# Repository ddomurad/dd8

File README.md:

# dd8
6502 based 8bit computer. 
TBD.

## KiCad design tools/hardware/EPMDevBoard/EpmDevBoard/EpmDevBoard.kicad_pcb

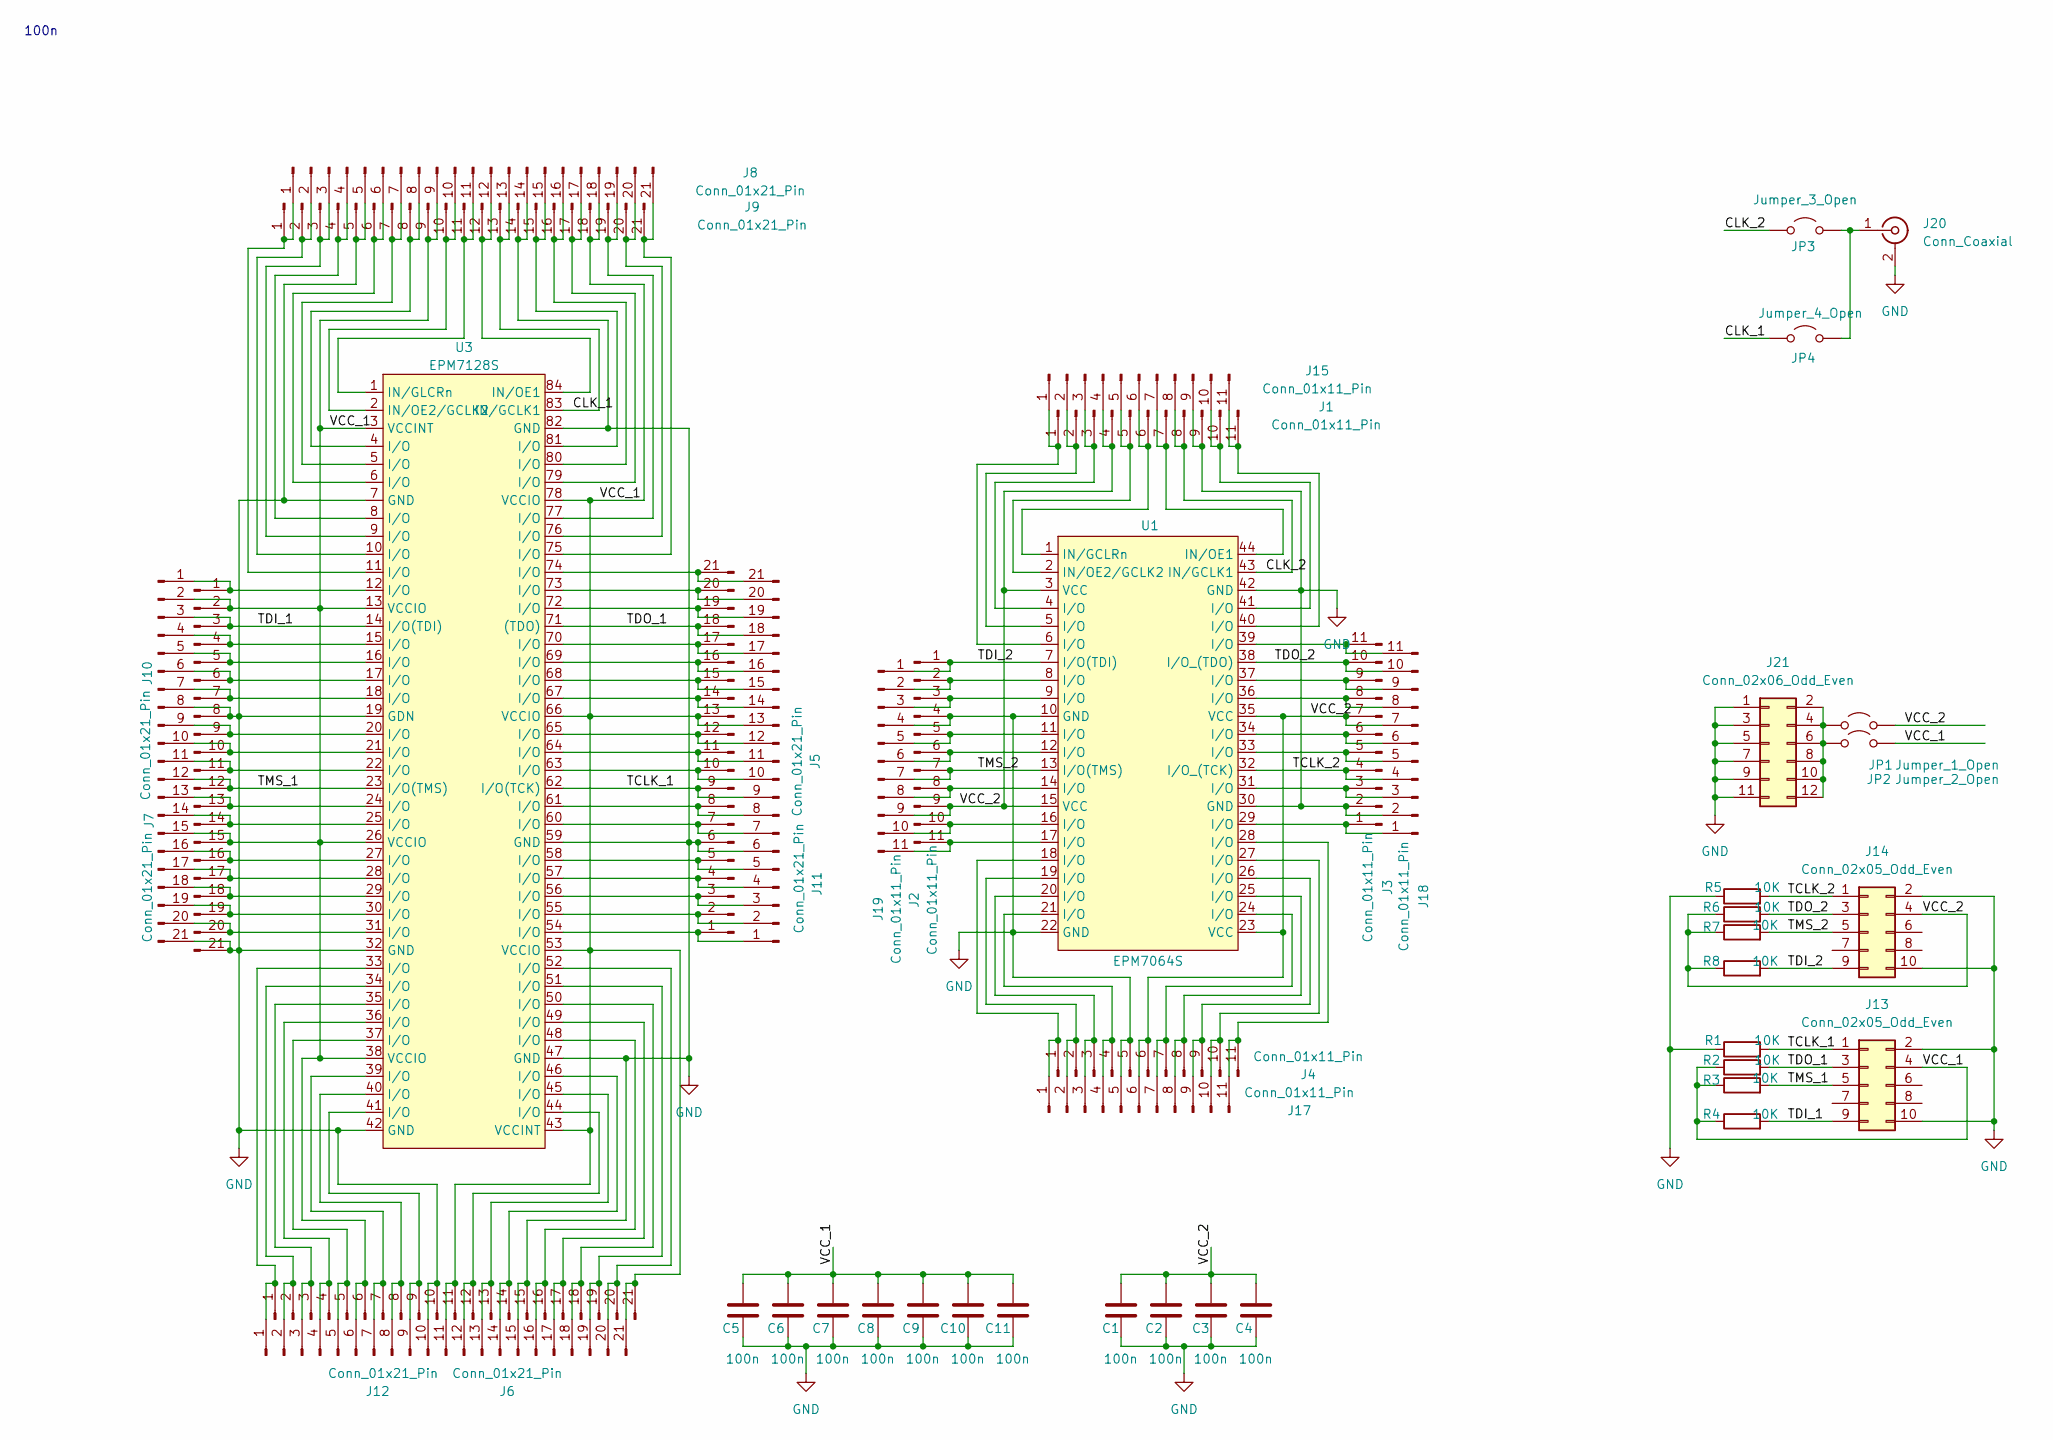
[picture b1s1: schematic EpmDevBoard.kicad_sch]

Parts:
C1, C2, C3, C4, C5, C6, C7, C8, C9, C10, C11: 100n; C_Disc_D3.0mm_W1.6mm_P2.50mm
J1, J2, J3, J4, J15, J17, J18, J19: Conn_01x11_Pin; PinHeader_1x11_P2.54mm_Vertical
J5, J6, J7, J8, J9, J10, J11, J12: Conn_01x21_Pin; PinSocket_1x21_P2.54mm_Vertical
J13, J14: Conn_02x05_Odd_Even; IDC-Header_2x05_P2.54mm_Vertical
J20: Conn_Coaxial; BNC_Amphenol_B6252HB-NPP3G-50_Horizontal
J21: Conn_02x06_Odd_Even; PinHeader_2x06_P2.54mm_Vertical
JP1: Jumper_1_Open; PinHeader_2x01_P2.54mm_Vertical
JP2: Jumper_2_Open; PinHeader_2x01_P2.54mm_Vertical
JP3: Jumper_3_Open; SolderJumper-2_P1.3mm_Open_Pad1.0x1.5mm
JP4: Jumper_4_Open; SolderJumper-2_P1.3mm_Open_Pad1.0x1.5mm
R1, R2, R3, R4, R5, R6, R7, R8: 10K; R_Axial_DIN0204_L3.6mm_D1.6mm_P5.08mm_Horizontal
U1: EPM7064S; PLCC-44_THT-Socket
U3: EPM7128S; PLCC-84_THT-Socket

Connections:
/CLK_1: J8.13, J9.13, JP4.1 (A), U3.83 (IN/GCLK1)
/CLK_2: J1.8, J15.8, JP3.1 (A), U1.43 (IN/GCLK1)
/TCLK_1: J5.9, J11.9, J13.1, R1.2, U3.62 (I/O(TCK))
/TCLK_2: J3.4, J14.1, J18.4, R5.2, U1.32 (I/O_(TCK))
/TDI_1: J7.3, J10.3, J13.9, R4.2, U3.14 (I/O(TDI))
/TDI_2: J2.1, J14.9, J19.1, R8.2, U1.7 (I/O(TDI))
/TDO_1: J5.18, J11.18, J13.3, R2.2, U3.71 ((TDO))
/TDO_2: J3.10, J14.3, J18.10, R6.2, U1.38 (I/O_(TDO))
/TMS_1: J7.12, J10.12, J13.5, R3.2, U3.23 (I/O(TMS))
/TMS_2: J2.7, J14.5, J19.7, R7.2, U1.13 (I/O(TMS))
/VCC_1: C5.1, C6.1, C7.1, C8.1, C9.1, C10.1, C11.1, J5.13, J6.6, J6.11, J6.21, J7.2, J7.15, J8.9, J8.18, J9.9, J9.18, J10.2, J10.15, J11.13, J12.6, J12.11, J12.21, J13.4, JP2.2 (B), R2.1, R3.1, R4.1, U3.3 (VCCINT), U3.13 (VCCIO), U3.26 (VCCIO), U3.38 (VCCIO), U3.43 (VCCINT), U3.53 (VCCIO), U3.66 (VCCIO), U3.78 (VCCIO)
/VCC_2: C1.1, C2.1, C3.1, C4.1, J1.4, J2.9, J3.7, J4.6, J14.4, J15.4, J17.6, J18.7, J19.9, JP1.2 (B), R6.1, R7.1, R8.1, U1.3 (VCC), U1.15 (VCC), U1.23 (VCC), U1.35 (VCC)
GND: C1.2, C2.2, C3.2, C4.2, C5.2, C6.2, C7.2, C8.2, C9.2, C10.2, C11.2, J1.9, J2.4, J3.2, J4.5, J5.6, J6.10, J6.15, J7.8, J7.21, J8.5, J8.14, J9.5, J9.14, J10.8, J10.21, J11.6, J12.10, J12.15, J13.2, J13.10, J14.2, J14.10, J15.9, J17.5, J18.2, J19.4, J20.2 (Ext), J21.1, J21.3, J21.5, J21.7, J21.9, J21.11, R1.1, R5.1, U1.10 (GND), U1.22 (GND), U1.30 (GND), U1.42 (GND), U3.7 (GND), U3.19 (GDN), U3.32 (GND), U3.42 (GND), U3.47 (GND), U3.59 (GND), U3.82 (GND)
unnamed: J1.1, J15.1, U1.6 (I/O)
unnamed: J1.2, J15.2, U1.5 (I/O)
unnamed: J1.3, J15.3, U1.4 (I/O)
unnamed: J1.5, J15.5, U1.2 (IN/OE2/GCLK2)
unnamed: J1.6, J15.6, U1.1 (IN/GCLRn)
unnamed: J1.7, J15.7, U1.44 (IN/OE1)
unnamed: J1.10, J15.10, U1.41 (I/O)
unnamed: J1.11, J15.11, U1.40 (I/O)
unnamed: J8.1, J9.1, U3.11 (I/O)
unnamed: J8.2, J9.2, U3.10 (I/O)
unnamed: J8.3, J9.3, U3.9 (I/O)
unnamed: J8.4, J9.4, U3.8 (I/O)
unnamed: J8.6, J9.6, U3.6 (I/O)
unnamed: J8.7, J9.7, U3.5 (I/O)
unnamed: J8.8, J9.8, U3.4 (I/O)
unnamed: J8.10, J9.10, U3.2 (IN/OE2/GCLK2)
unnamed: J8.11, J9.11, U3.1 (IN/GLCRn)
unnamed: J8.12, J9.12, U3.84 (IN/OE1)
unnamed: J8.15, J9.15, U3.81 (I/O)
unnamed: J8.16, J9.16, U3.80 (I/O)
unnamed: J8.17, J9.17, U3.79 (I/O)
unnamed: J8.19, J9.19, U3.77 (I/O)
unnamed: J8.20, J9.20, U3.76 (I/O)
unnamed: J8.21, J9.21, U3.75 (I/O)
unnamed: J7.1, J10.1, U3.12 (I/O)
unnamed: J7.4, J10.4, U3.15 (I/O)
unnamed: J7.5, J10.5, U3.16 (I/O)
unnamed: J7.6, J10.6, U3.17 (I/O)
unnamed: J7.7, J10.7, U3.18 (I/O)
unnamed: J7.9, J10.9, U3.20 (I/O)
unnamed: J7.10, J10.10, U3.21 (I/O)
unnamed: J7.11, J10.11, U3.22 (I/O)
unnamed: J7.13, J10.13, U3.24 (I/O)
unnamed: J7.14, J10.14, U3.25 (I/O)
unnamed: J7.16, J10.16, U3.27 (I/O)
unnamed: J7.17, J10.17, U3.28 (I/O)
unnamed: J7.18, J10.18, U3.29 (I/O)
unnamed: J7.19, J10.19, U3.30 (I/O)
unnamed: J7.20, J10.20, U3.31 (I/O)
unnamed: J5.1, J11.1, U3.54 (I/O)
unnamed: J5.2, J11.2, U3.55 (I/O)
unnamed: J5.3, J11.3, U3.56 (I/O)
unnamed: J5.4, J11.4, U3.57 (I/O)
unnamed: J5.5, J11.5, U3.58 (I/O)
unnamed: J5.7, J11.7, U3.60 (I/O)
unnamed: J5.8, J11.8, U3.61 (I/O)
unnamed: J5.10, J11.10, U3.63 (I/O)
unnamed: J5.11, J11.11, U3.64 (I/O)
unnamed: J5.12, J11.12, U3.65 (I/O)
unnamed: J5.14, J11.14, U3.67 (I/O)
unnamed: J5.15, J11.15, U3.68 (I/O)
unnamed: J5.16, J11.16, U3.69 (I/O)
unnamed: J5.17, J11.17, U3.70 (I/O)
unnamed: J5.19, J11.19, U3.72 (I/O)
unnamed: J5.20, J11.20, U3.73 (I/O)
unnamed: J5.21, J11.21, U3.74 (I/O)
unnamed: J6.1, J12.1, U3.33 (I/O)
unnamed: J6.2, J12.2, U3.34 (I/O)
unnamed: J6.3, J12.3, U3.35 (I/O)
unnamed: J6.4, J12.4, U3.36 (I/O)
unnamed: J6.5, J12.5, U3.37 (I/O)
unnamed: J6.7, J12.7, U3.39 (I/O)
unnamed: J6.8, J12.8, U3.40 (I/O)
unnamed: J6.9, J12.9, U3.41 (I/O)
unnamed: J6.12, J12.12, U3.44 (I/O)
unnamed: J6.13, J12.13, U3.45 (I/O)
unnamed: J6.14, J12.14, U3.46 (I/O)
unnamed: J6.16, J12.16, U3.48 (I/O)
unnamed: J6.17, J12.17, U3.49 (I/O)
unnamed: J6.18, J12.18, U3.50 (I/O)
unnamed: J6.19, J12.19, U3.51 (I/O)
unnamed: J6.20, J12.20, U3.52 (I/O)
unnamed: J4.1, J17.1, U1.18 (I/O)
unnamed: J4.2, J17.2, U1.19 (I/O)
unnamed: J4.3, J17.3, U1.20 (I/O)
unnamed: J4.4, J17.4, U1.21 (I/O)
unnamed: J4.7, J17.7, U1.24 (I/O)
unnamed: J4.8, J17.8, U1.25 (I/O)
unnamed: J4.9, J17.9, U1.26 (I/O)
unnamed: J4.10, J17.10, U1.27 (I/O)
unnamed: J4.11, J17.11, U1.28 (I/O)
unnamed: J3.1, J18.1, U1.29 (I/O)
unnamed: J3.3, J18.3, U1.31 (I/O)
unnamed: J3.5, J18.5, U1.33 (I/O)
unnamed: J3.6, J18.6, U1.34 (I/O)
unnamed: J3.8, J18.8, U1.36 (I/O)
unnamed: J3.9, J18.9, U1.37 (I/O)
unnamed: J3.11, J18.11, U1.39 (I/O)
unnamed: J2.2, J19.2, U1.8 (I/O)
unnamed: J2.3, J19.3, U1.9 (I/O)
unnamed: J2.5, J19.5, U1.11 (I/O)
unnamed: J2.6, J19.6, U1.12 (I/O)
unnamed: J2.8, J19.8, U1.14 (I/O)
unnamed: J2.10, J19.10, U1.16 (I/O)
unnamed: J2.11, J19.11, U1.17 (I/O)
unnamed: J20.1 (In), JP3.2 (B), JP4.2 (B)
unnamed: J21.2, J21.4, J21.6, J21.8, J21.10, J21.12, JP1.1 (A), JP2.1 (A)

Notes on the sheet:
100n

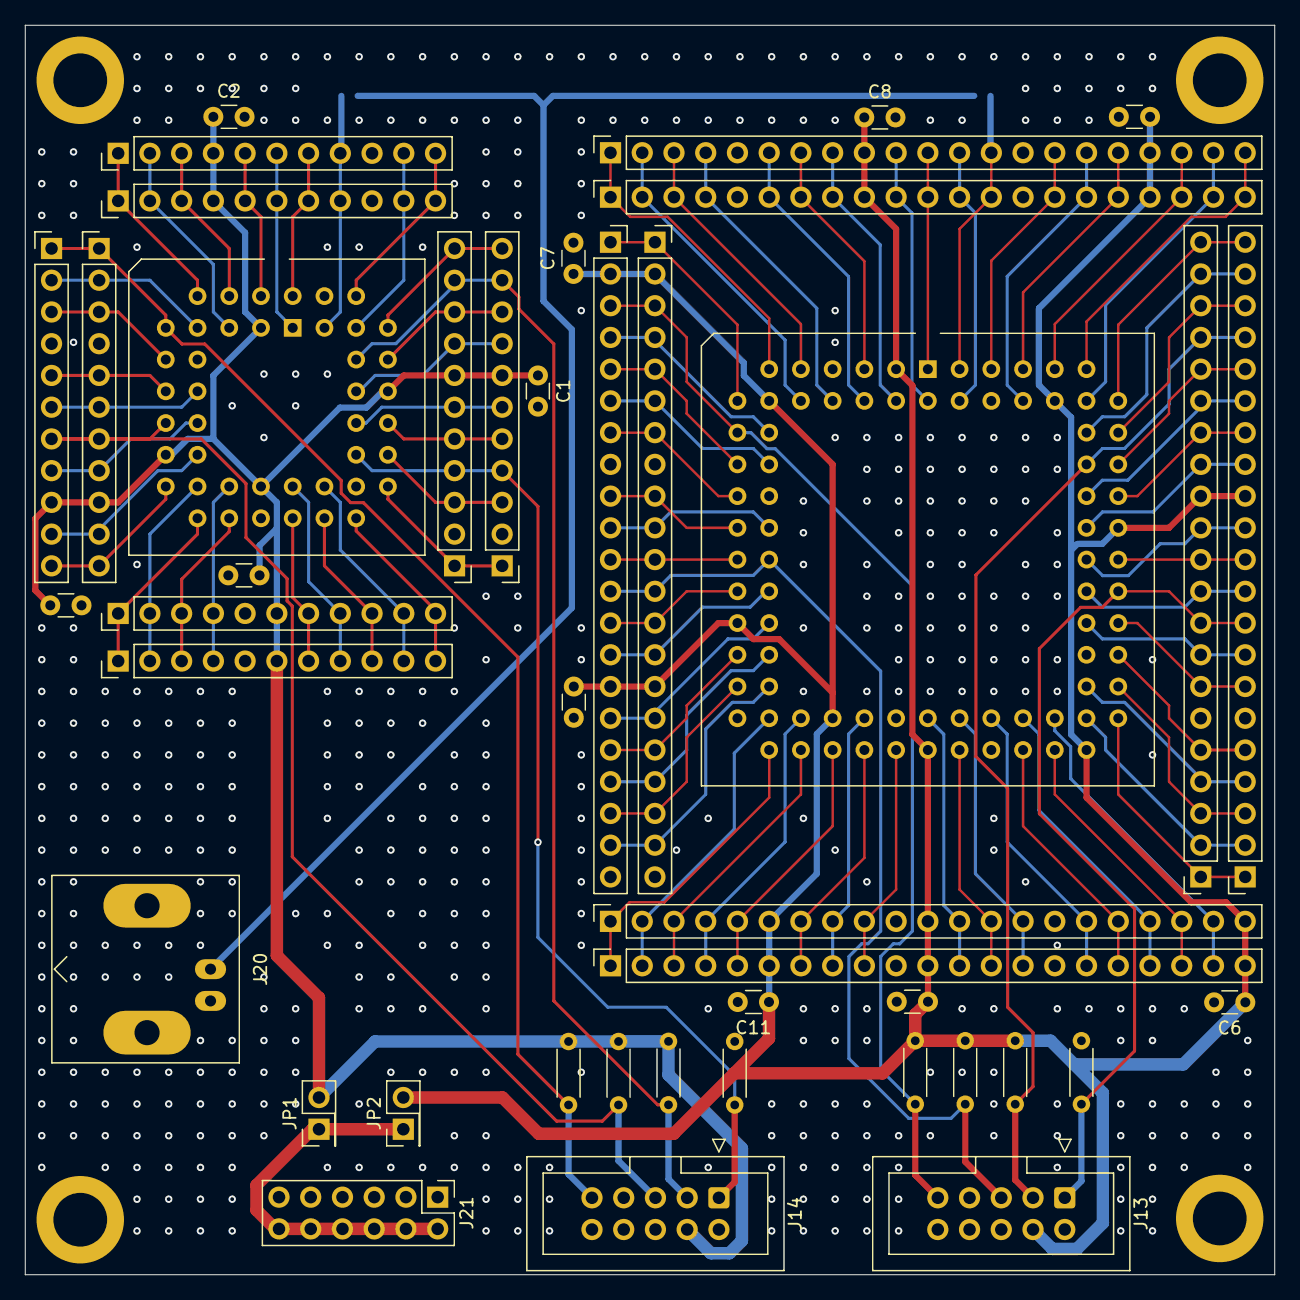
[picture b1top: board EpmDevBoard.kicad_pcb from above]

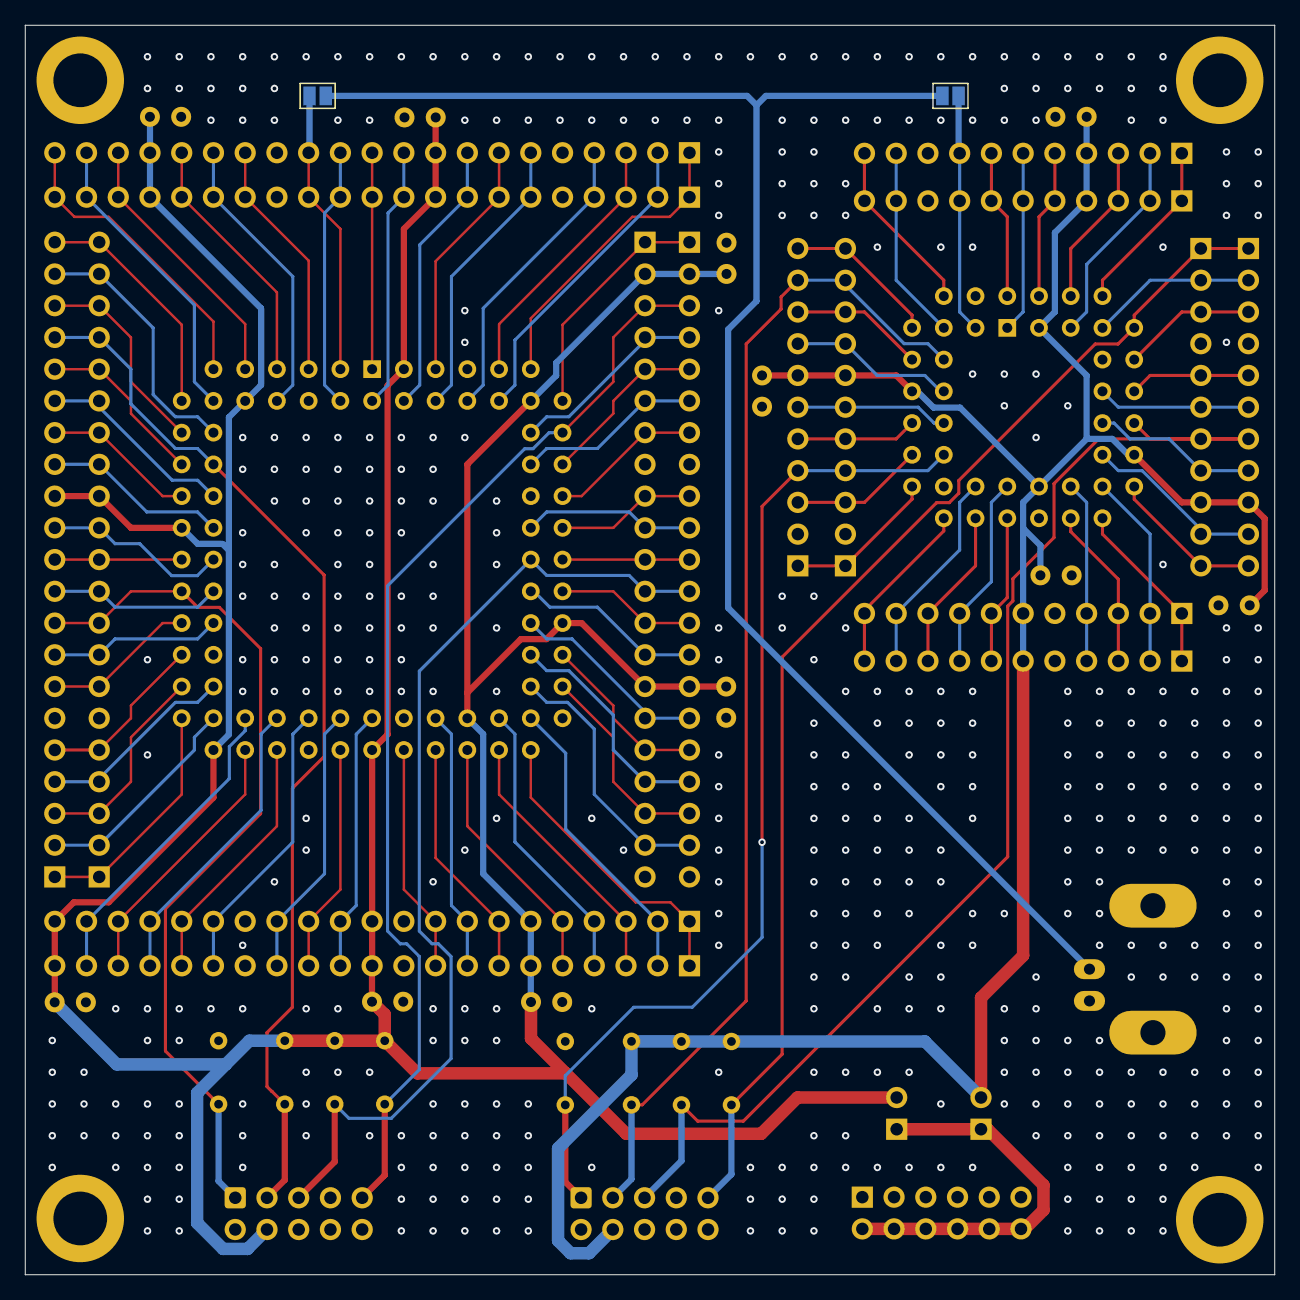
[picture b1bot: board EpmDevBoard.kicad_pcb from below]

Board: 4 copper layers, 100.0 x 100.0 mm, 45 parts (2 on the bottom side), 110 nets.

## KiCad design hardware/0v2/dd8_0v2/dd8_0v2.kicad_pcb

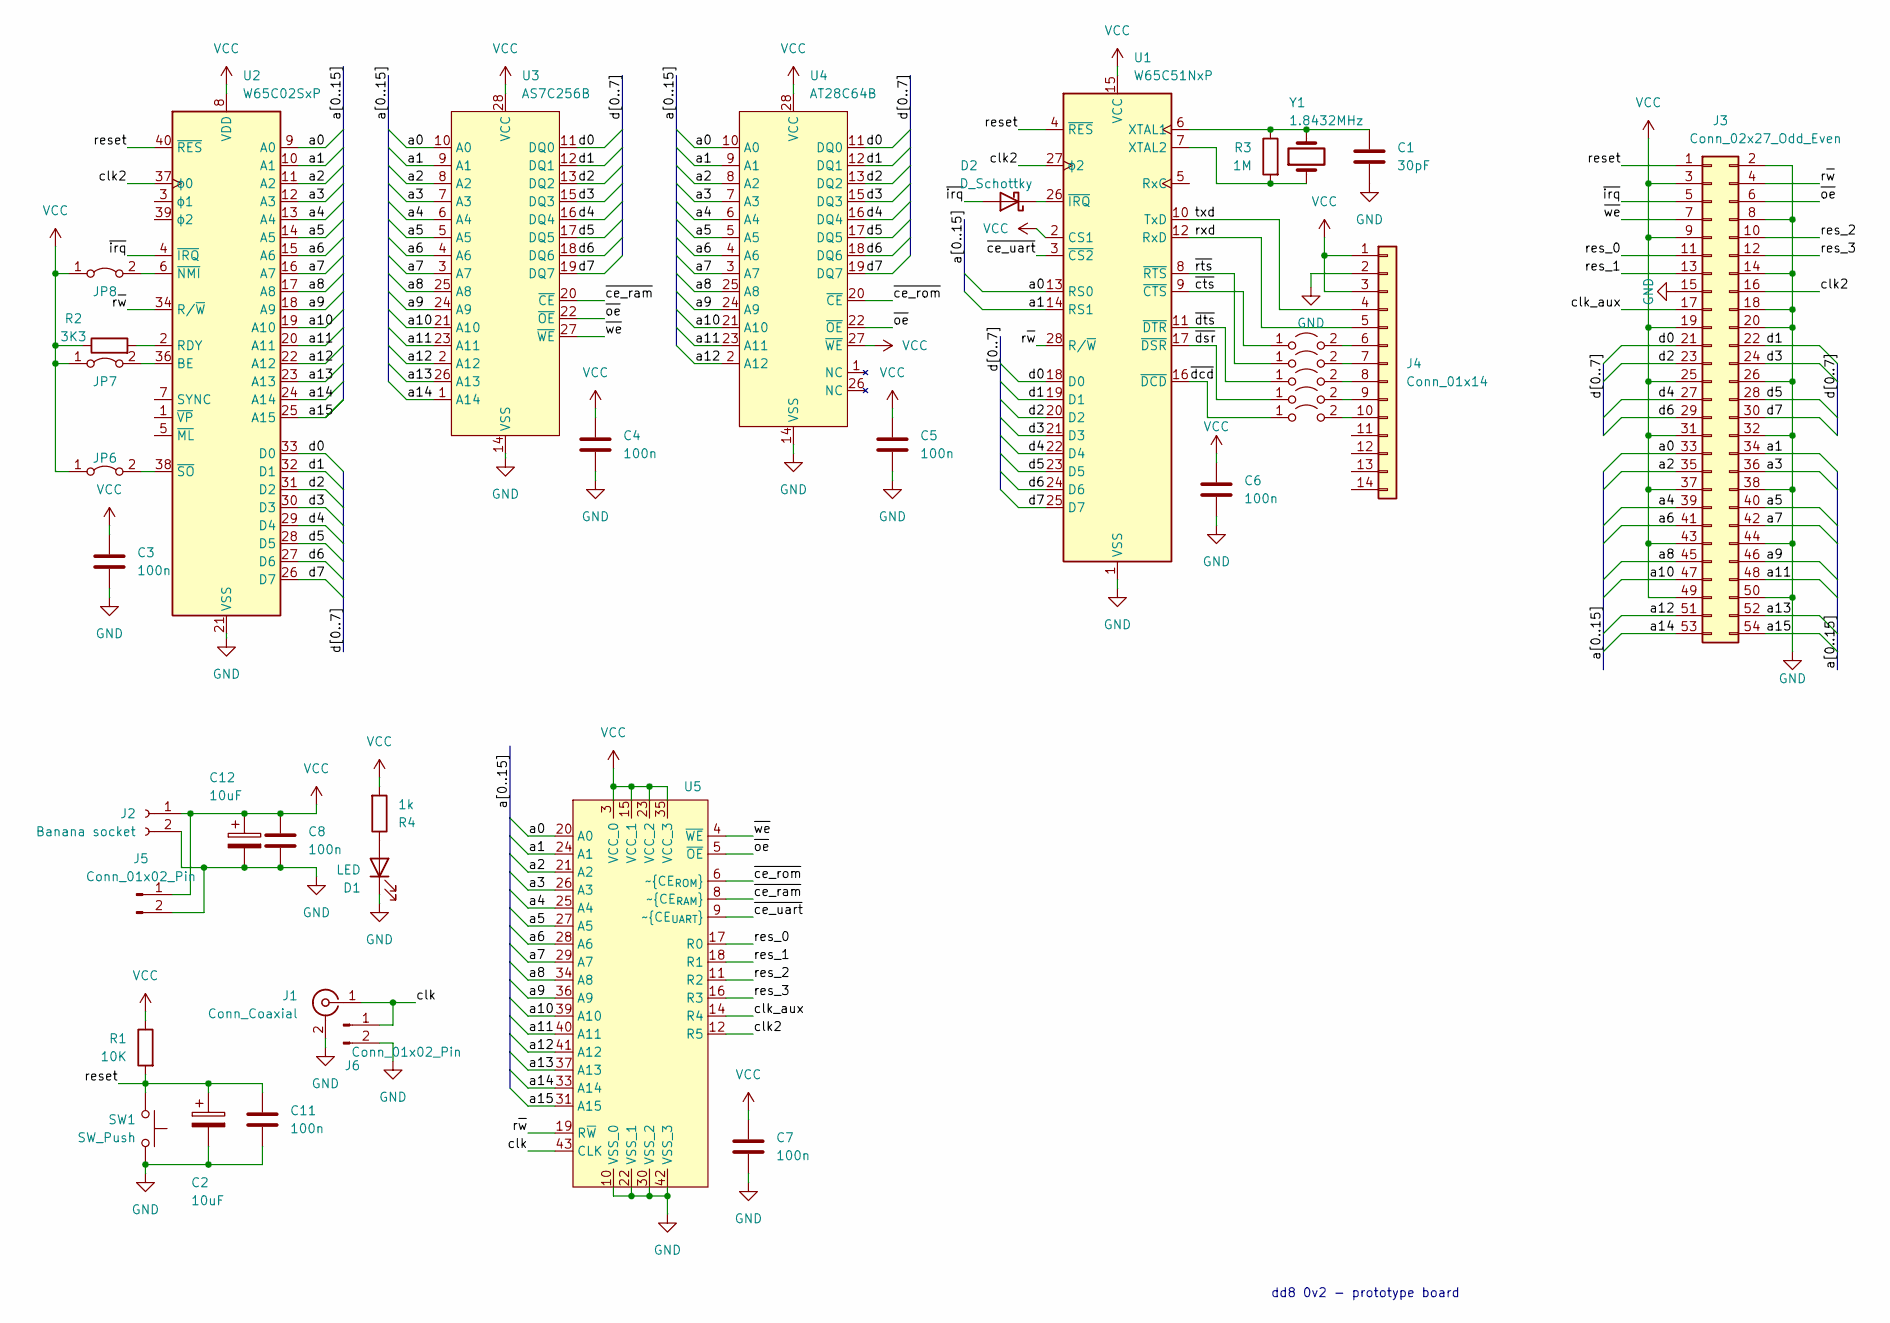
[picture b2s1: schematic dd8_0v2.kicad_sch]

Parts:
C1: 30pF; C_Disc_D3.0mm_W1.6mm_P2.50mm
C2, C12: 10uF; CP_Radial_D5.0mm_P2.50mm
C3, C4, C5, C6, C7, C8, C11: 100n; C_Disc_D3.0mm_W1.6mm_P2.50mm
D1: LED; LED_D3.0mm
D2: D_Schottky; D_DO-35_SOD27_P7.62mm_Horizontal
J1: Conn_Coaxial; BNC_Amphenol_B6252HB-NPP3G-50_Horizontal
J2: Banana socket; Bannana_Jack_2Pin
J3: Conn_02x27_Odd_Even; PinSocket_2x27_P2.54mm_Vertical
J4: Conn_01x14; PinHeader_2x07_P2.54mm_Vertical
J5, J6: Conn_01x02_Pin; PinSocket_1x02_P2.54mm_Vertical
JP1, JP2, JP3, JP4, JP5: Jumper_2_Open; SolderJumper-2_P1.3mm_Open_Pad1.0x1.5mm
JP6, JP7, JP8: Jumper_2_Bridged; PinHeader_1x02_P2.54mm_Vertical
R1: 10K; R_Axial_DIN0204_L3.6mm_D1.6mm_P2.54mm_Vertical
R2: 3K3; R_Axial_DIN0204_L3.6mm_D1.6mm_P2.54mm_Vertical
R3: 1M; R_Axial_DIN0204_L3.6mm_D1.6mm_P5.08mm_Horizontal
R4: 1k; R_Axial_DIN0204_L3.6mm_D1.6mm_P2.54mm_Vertical
SW1: SW_Push; SW_PUSH_6mm_H5mm
U1: W65C51NxP; DIP-28_W15.24mm
U2: W65C02SxP; DIP-40_W15.24mm
U3: AS7C256B; DIP-28_W7.62mm
U4: AT28C64B; DIP_Socket-28_W11.9_W12.7_W15.24_W17.78_W18.5_3M_228-1277-0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
U5: PLCC-44_THT-Socket
Y1: 1.8432MHz; Crystal_HC18-U_Vertical

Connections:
/a0: J3.33, U1.13 (RS0), U2.9 (A0), U3.10 (A0), U4.10 (A0), U5.20 (A0)
/a1: J3.34, U1.14 (RS1), U2.10 (A1), U3.9 (A1), U4.9 (A1), U5.24 (A1)
/a2: J3.35, U2.11 (A2), U3.8 (A2), U4.8 (A2), U5.21 (A2)
/a3: J3.36, U2.12 (A3), U3.7 (A3), U4.7 (A3), U5.26 (A3)
/a4: J3.39, U2.13 (A4), U3.6 (A4), U4.6 (A4), U5.25 (A4)
/a5: J3.40, U2.14 (A5), U3.5 (A5), U4.5 (A5), U5.27 (A5)
/a6: J3.41, U2.15 (A6), U3.4 (A6), U4.4 (A6), U5.28 (A6)
/a7: J3.42, U2.16 (A7), U3.3 (A7), U4.3 (A7), U5.29 (A7)
/a8: J3.45, U2.17 (A8), U3.25 (A8), U4.25 (A8), U5.34 (A8)
/a9: J3.46, U2.18 (A9), U3.24 (A9), U4.24 (A9), U5.36 (A9)
/a10: J3.47, U2.19 (A10), U3.21 (A10), U4.21 (A10), U5.39 (A10)
/a11: J3.48, U2.20 (A11), U3.23 (A11), U4.23 (A11), U5.40 (A11)
/a12: J3.51, U2.22 (A12), U3.2 (A12), U4.2 (A12), U5.41 (A12)
/a13: J3.52, U2.23 (A13), U3.26 (A13), U5.37 (A13)
/a14: J3.53, U2.24 (A14), U3.1 (A14), U5.33 (A14)
/a15: J3.54, U2.25 (A15), U5.31 (A15)
/clk: J1.1 (In), J6.1, U5.43 (CLK)
/clk2: J3.16, U1.27 (ϕ2), U2.37 (ϕ0), U5.12 (R5)
/clk_aux: J3.17, U5.14 (R4)
/d0: J3.21, U1.18 (D0), U2.33 (D0), U3.11 (DQ0), U4.11 (DQ0)
/d1: J3.22, U1.19 (D1), U2.32 (D1), U3.12 (DQ1), U4.12 (DQ1)
/d2: J3.23, U1.20 (D2), U2.31 (D2), U3.13 (DQ2), U4.13 (DQ2)
/d3: J3.24, U1.21 (D3), U2.30 (D3), U3.15 (DQ3), U4.15 (DQ3)
/d4: J3.27, U1.22 (D4), U2.29 (D4), U3.16 (DQ4), U4.16 (DQ4)
/d5: J3.28, U1.23 (D5), U2.28 (D5), U3.17 (DQ5), U4.17 (DQ5)
/d6: J3.29, U1.24 (D6), U2.27 (D6), U3.18 (DQ6), U4.18 (DQ6)
/d7: J3.30, U1.25 (D7), U2.26 (D7), U3.19 (DQ7), U4.19 (DQ7)
/res_0: J3.11, U5.17 (R0)
/res_1: J3.13, U5.18 (R1)
/res_2: J3.10, U5.11 (R2)
/res_3: J3.12, U5.16 (R3)
/reset: C2.1, C11.1, J3.1, R1.2, SW1.2, U1.4 (~RES), U2.40 (~RES)
/rxd: J4.5, U1.12 (RxD)
/r~w: J3.4, U1.28 (R/~W), U2.34 (R/~W), U5.19 (R~W)
/txd: J4.4, U1.10 (TxD)
/~ce_ram: U3.20 (~CE), U5.8 (~CE_{RAM})
/~ce_rom: U4.20 (~CE), U5.6 (~CE_{ROM})
/~ce_uart: U1.3 (~CS2), U5.9 (~CE_{UART})
/~cts: JP1.1 (A), U1.9 (~CTS)
/~dcd: JP5.1 (A), U1.16 (~DCD)
/~dsr: JP4.1 (A), U1.17 (~DSR)
/~dts: JP3.1 (A), U1.11 (~DTR)
/~irq: D2.2 (A), J3.5, U2.4 (~IRQ)
/~oe: J3.6, U3.22 (~OE), U4.22 (~OE), U5.5 (~OE)
/~rts: JP2.1 (A), U1.8 (~RTS)
/~we: J3.7, U3.27 (~WE), U5.4 (~WE)
GND: C1.2, C2.2, C3.2, C4.2, C5.2, C6.2, C7.2, C8.2, C11.2, C12.2, D1.1 (K), J1.2 (Ext), J2.2, J3.2, J3.8, J3.14, J3.15, J3.18, J3.20, J3.26, J3.32, J3.38, J3.44, J3.50, J4.2, J5.2, J6.2, SW1.1, U1.1 (VSS), U2.21 (VSS), U3.14 (VSS), U4.14 (VSS), U5.10 (VSS_0), U5.22 (VSS_1), U5.30 (VSS_2), U5.42 (VSS_3)
unnamed: D1.2 (A), R4.1
unnamed: D2.1 (K), U1.26 (~IRQ)
unnamed: J4.6, JP1.2 (B)
unnamed: J4.7, JP2.2 (B)
unnamed: J4.8, JP3.2 (B)
unnamed: J4.9, JP4.2 (B)
unnamed: J4.10, JP5.2 (B)
unnamed: JP6.2 (B), U2.38 (~SO)
unnamed: JP7.2 (B), U2.36 (BE)
unnamed: JP8.2 (B), U2.6 (~NMI)
unnamed: C1.1, R3.1, U1.6 (XTAL1), Y1.2
unnamed: R3.2, U1.7 (XTAL2), Y1.1
unnamed: R2.2, U2.2 (RDY)
VCC: C3.1, C4.1, C5.1, C6.1, C7.1, C8.1, C12.1, J2.1, J3.3, J3.9, J3.19, J3.25, J3.31, J3.37, J3.43, J3.49, J4.1, J4.3, J5.1, JP6.1 (A), JP7.1 (A), JP8.1 (A), R1.1, R2.1, R4.2, U1.2 (CS1), U1.15 (VCC), U2.8 (VDD), U3.28 (VCC), U4.27 (~WE), U4.28 (VCC), U5.3 (VCC_0), U5.15 (VCC_1), U5.23 (VCC_2), U5.35 (VCC_3)

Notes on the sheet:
dd8 0v2 - prototype board

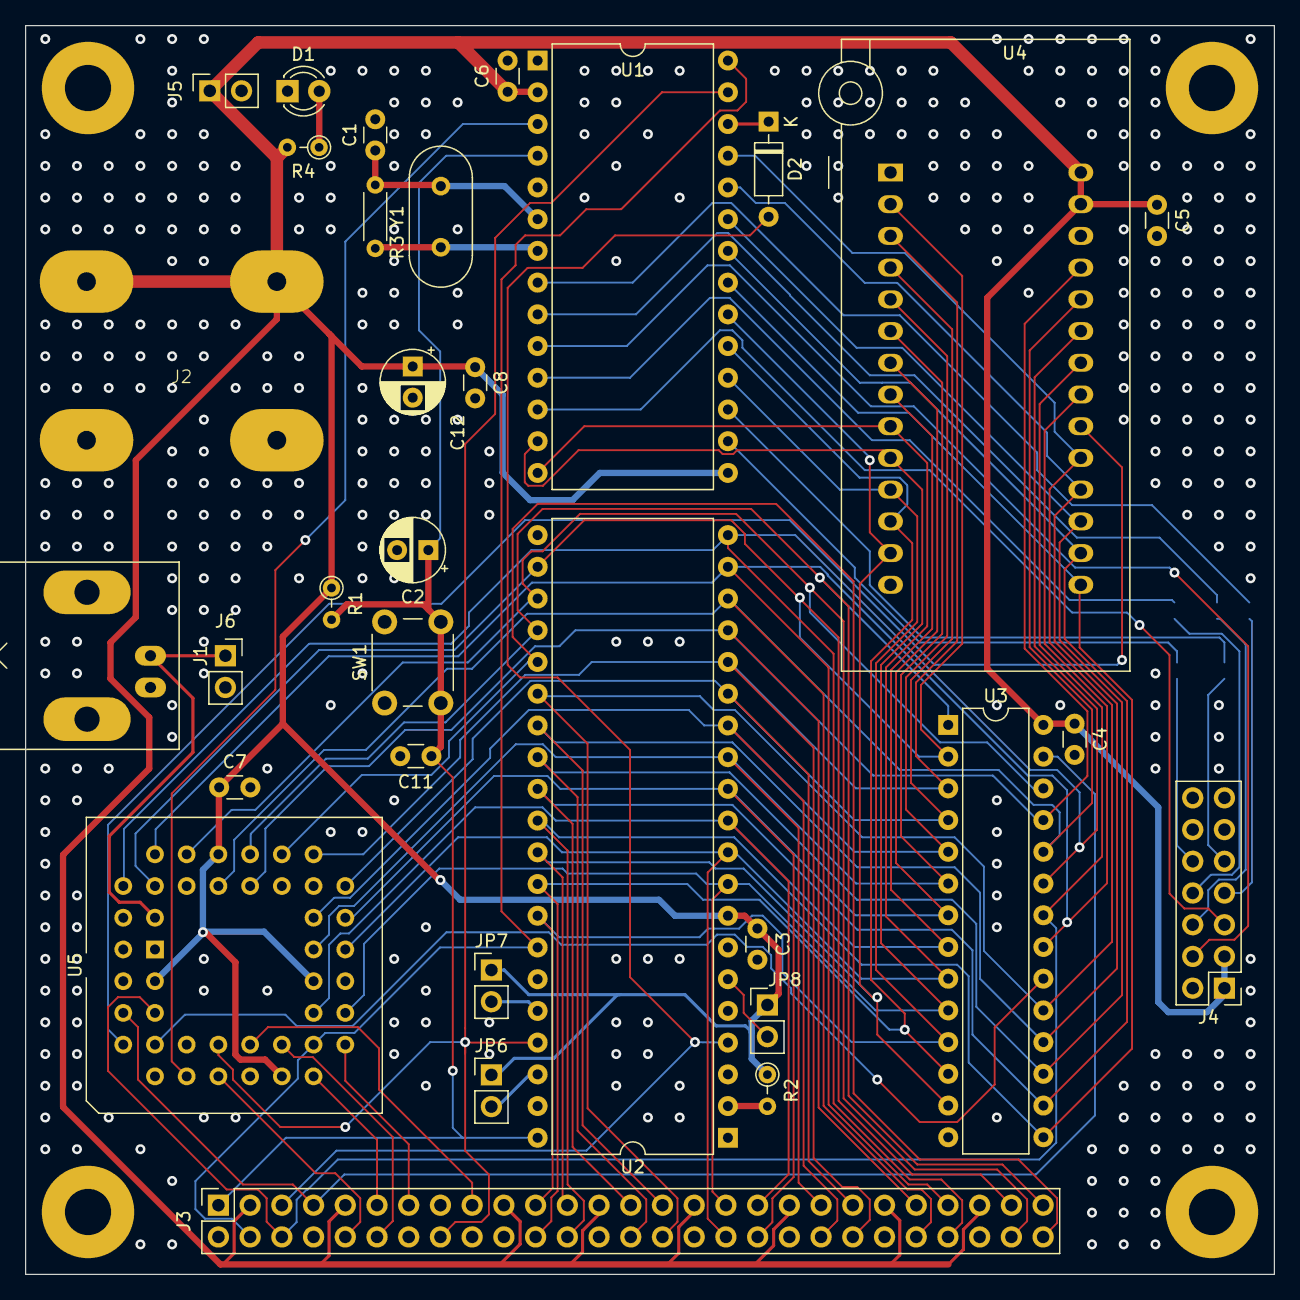
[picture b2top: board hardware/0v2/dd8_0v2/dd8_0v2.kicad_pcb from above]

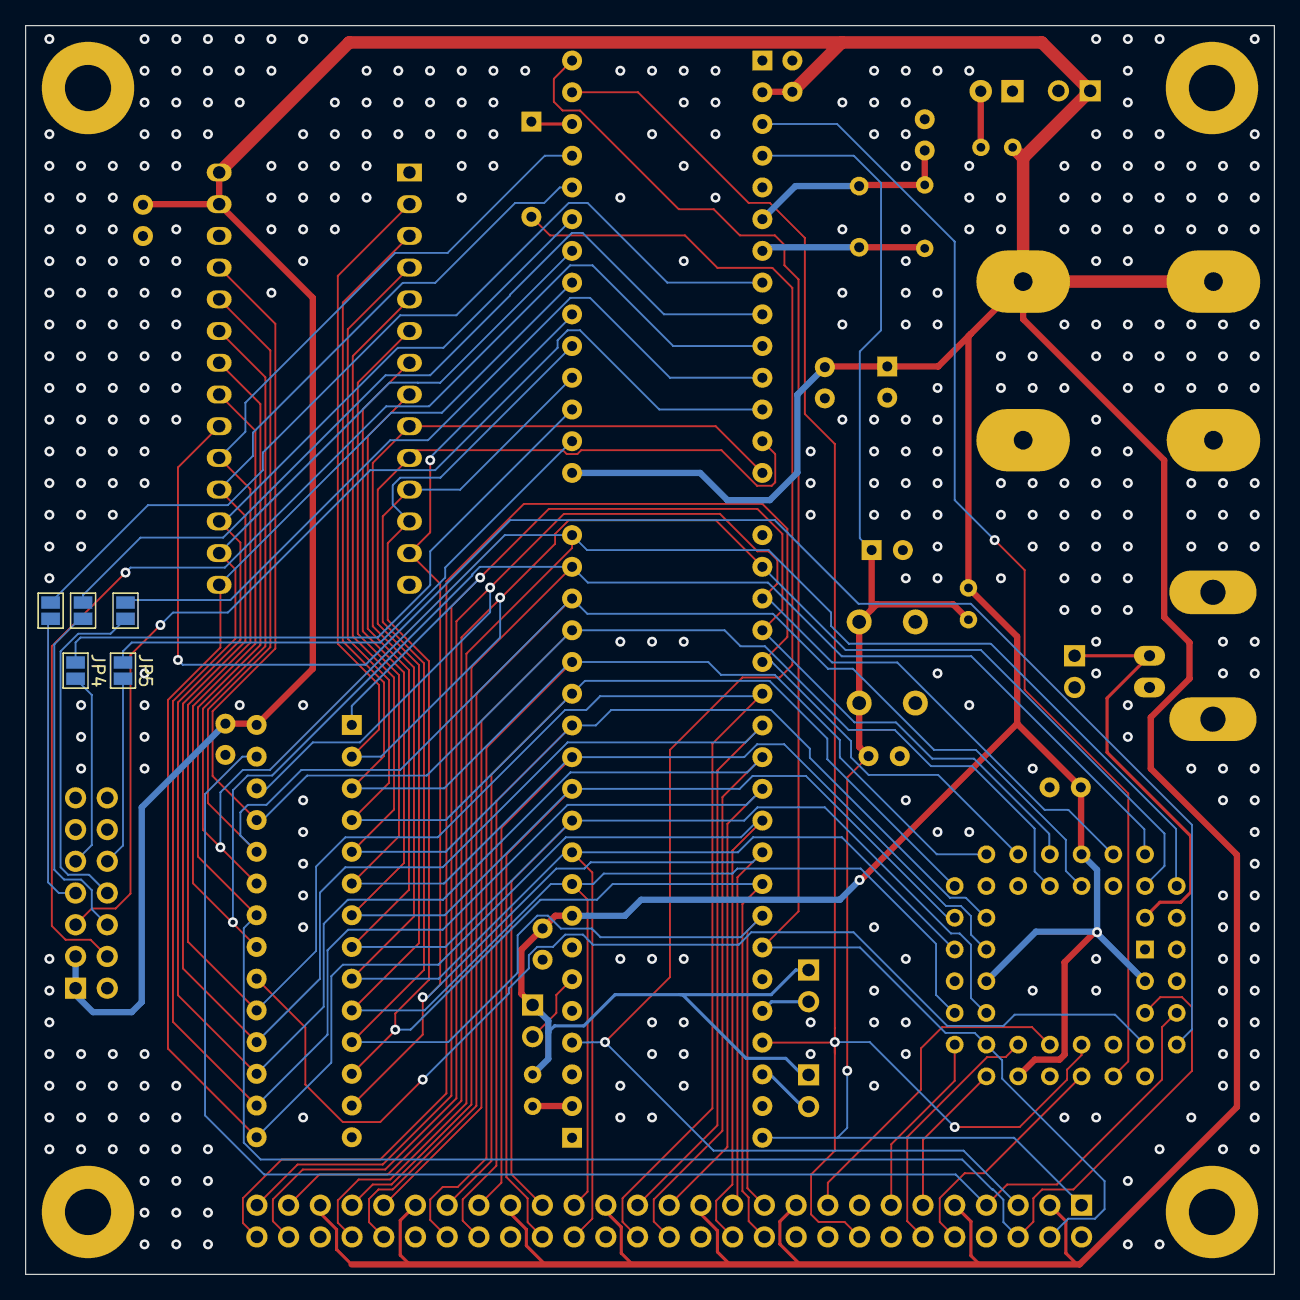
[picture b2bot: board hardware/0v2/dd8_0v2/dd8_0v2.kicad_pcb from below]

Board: 4 copper layers, 100.0 x 100.0 mm, 37 parts (5 on the bottom side), 61 nets.
